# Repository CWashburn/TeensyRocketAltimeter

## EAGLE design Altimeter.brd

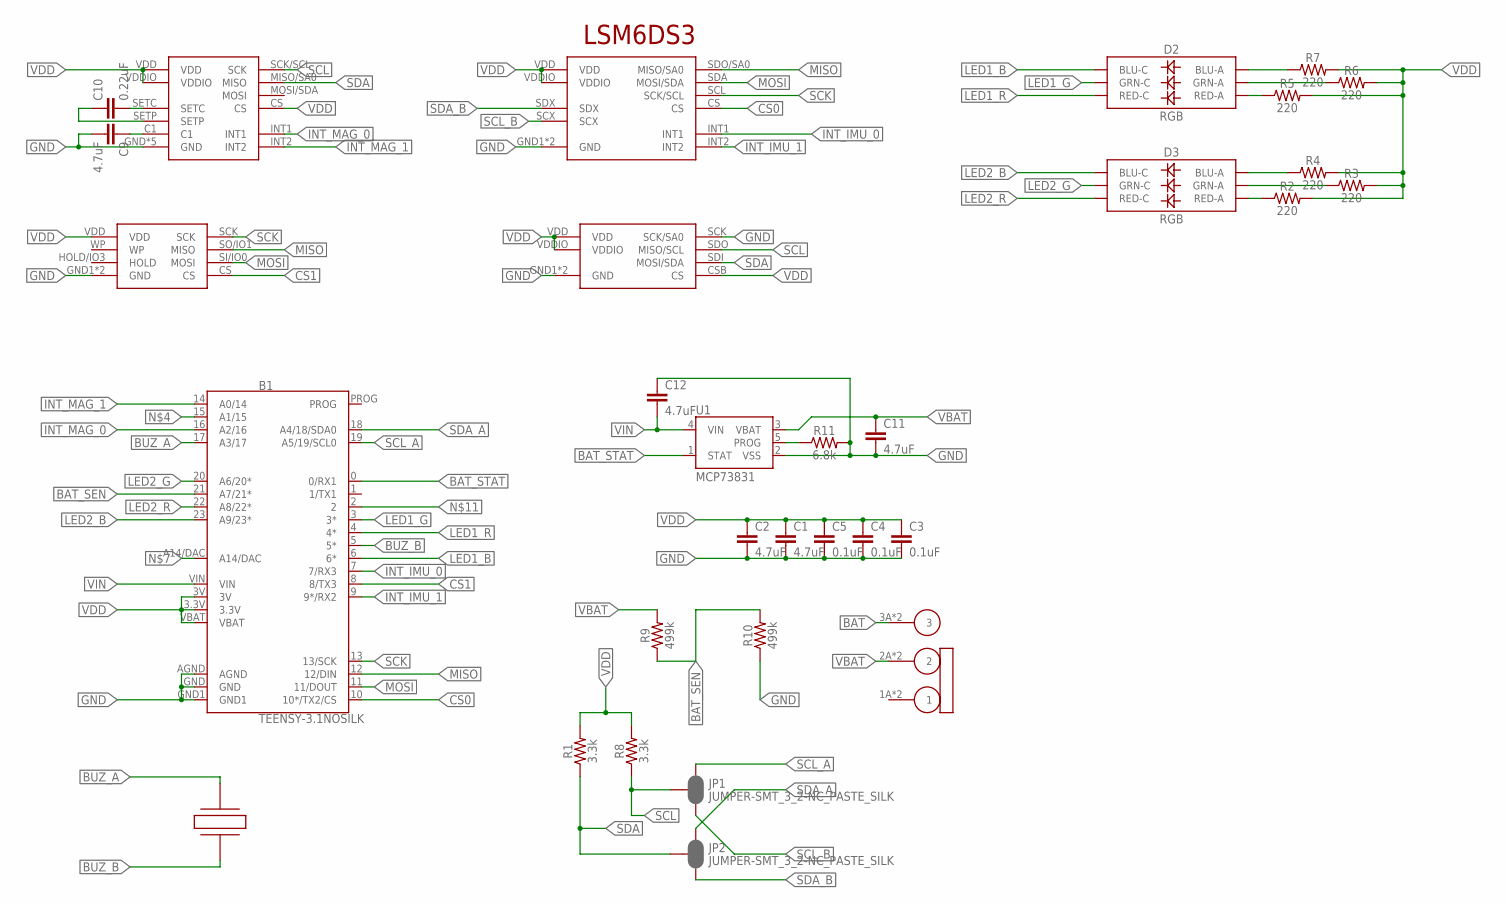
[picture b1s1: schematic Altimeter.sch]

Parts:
B1: TEENSY-3.1NOSILK; TEENSY-3.1_NOSILK
C1, C2, C9, C11, C12: 4.7uF; 0603
C3, C4, C5: 0.1uF; 0603
C10: 0.22uF; 0603
D2, D3: RGB; PLCC-6-LED
JP1, JP2: JUMPER-SMT_3_2-NC_PASTE_SILK; SMT-JUMPER_3_2-NC_PASTE_SILK
R1, R8: 3.3k; 0603
R2, R3, R4, R5, R6, R7: 220; 0603
R9, R10: 499k; 0603
R11: 6.8k; 0603
U1: MCP73831; SOT23-5
U$1: BMP280
U$3: JS102011JAQN
U$5: LSM6DS3
U$6: LSM303D
U$7: PKLCS1212
U$8: S25FL256S

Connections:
BAT: U$3.3A (3), U$3.3B (3)
BAT_SEN: B1.21 (A7/21*), R9.1, R10.2
BAT_STAT: B1.0 (0/RX1), U1.1 (STAT)
BUZ_A: B1.17 (A3/17), U$7.2
BUZ_B: B1.5 (5*), U$7.1
CS0: B1.10 (10*/TX2/CS), U$5.CS
CS1: B1.8 (8/TX3), U$8.CS
GND: B1.AGND, B1.GND, B1.GND1, C1.2, C2.2, C3.2, C4.2, C5.2, C9.2, C11.2, C12.1, R10.1, R11.2, U1.2 (VSS), U$1.GND1 (GND), U$1.GND2 (GND), U$1.SCK (SCK/SA0), U$5.GND1 (GND), U$5.GND2 (GND), U$6.GND, U$6.GND1 (GND), U$6.GND2 (GND), U$6.GND3 (GND), U$6.GND4 (GND), U$8.GND1 (GND), U$8.GND2 (GND)
INT_IMU_0: B1.7 (7/RX3), U$5.INT1
INT_IMU_1: B1.9 (9*/RX2), U$5.INT2
INT_MAG_0: B1.16 (A2/16), U$6.INT1
INT_MAG_1: B1.14 (A0/14), U$6.INT2
LED1_B: B1.6 (6*), D2.CB (BLU-C)
LED1_G: B1.3 (3*), D2.CG (GRN-C)
LED1_R: B1.4 (4*), D2.CR (RED-C)
LED2_B: B1.23 (A9/23*), D3.CB (BLU-C)
LED2_G: B1.20 (A6/20*), D3.CG (GRN-C)
LED2_R: B1.22 (A8/22*), D3.CR (RED-C)
MISO: B1.12 (12/DIN), U$5.SDO/SA0 (MISO/SA0), U$8.SO/IO1 (MISO)
MOSI: B1.11 (11/DOUT), U$5.SDA (MOSI/SDA), U$8.SI/IO0 (MOSI)
unnamed: D2.AB (BLU-A), R7.1
unnamed: D2.AG (GRN-A), R6.1
unnamed: R11.1, U1.5 (PROG)
unnamed: D2.AR (RED-A), R5.1
unnamed: D3.AB (BLU-A), R4.1
unnamed: D3.AG (GRN-A), R3.1
unnamed: D3.AR (RED-A), R2.1
unnamed: C10.2, U$6.SETC
unnamed: C10.1, U$6.SETP
unnamed: C9.1, U$6.C1
SCK: B1.13 (13/SCK), U$5.SCL (SCK/SCL), U$8.SCK
SCL: JP1.2, R8.1, U$1.SDO (MISO/SCL), U$6.SCK/SCL (SCK)
SCL_A: B1.19 (A5/19/SCL0), JP1.1
SCL_B: JP1.3, U$5.SCX
SDA: JP2.2, R1.1, U$1.SDI (MOSI/SDA), U$6.MISO/SA0 (MISO)
SDA_A: B1.18 (A4/18/SDA0), JP2.1
SDA_B: JP2.3, U$5.SDX
VBAT: C11.1, R9.2, U1.3 (VBAT), U$3.2A (2), U$3.2B (2)
VDD: B1.3.3V, B1.3V, B1.VBAT, C1.1, C2.1, C3.1, C4.1, C5.1, R1.2, R2.2, R3.2, R4.2, R5.2, R6.2, R7.2, R8.2, U$1.CSB (CS), U$1.VDD, U$1.VDDIO, U$5.VDD, U$5.VDDIO, U$6.CS, U$6.VDD, U$6.VDDIO, U$8.VDD
VIN: B1.VIN, C12.2, U1.4 (VIN)

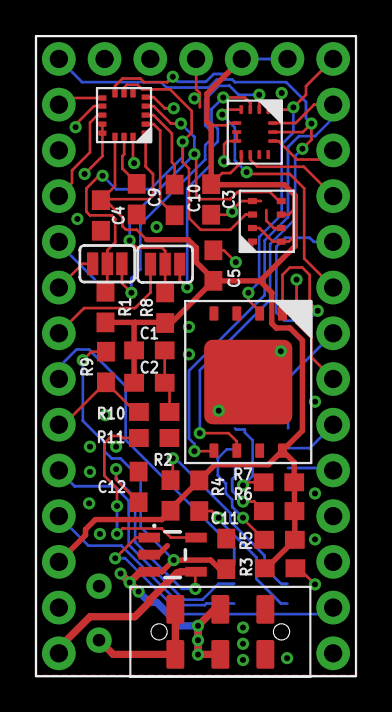
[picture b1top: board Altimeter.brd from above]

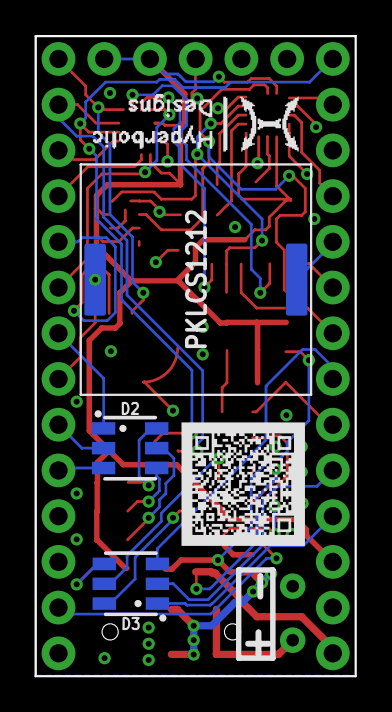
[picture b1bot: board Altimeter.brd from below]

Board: 2 copper layers, 17.8 x 35.6 mm, 32 parts (3 on the bottom side), 40 nets.

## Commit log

2017-03-22 Added eagle files

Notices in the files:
parts and their libraries:
SparkFun-Boards: Licensing: Creative Commons ShareAlike 4.0 International - https://creativecommons.org/licenses/by-sa/4.0
